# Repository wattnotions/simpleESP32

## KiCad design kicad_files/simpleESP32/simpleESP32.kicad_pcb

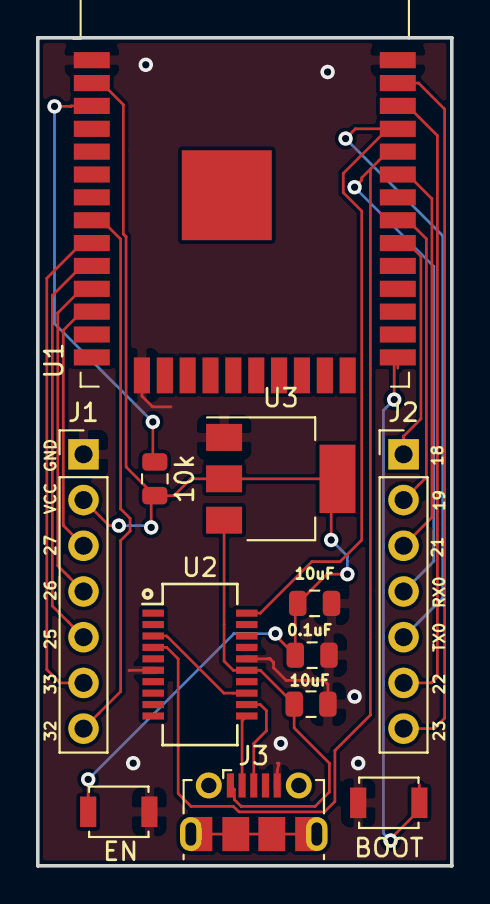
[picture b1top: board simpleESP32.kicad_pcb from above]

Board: 2 copper layers, 23.0 x 46.0 mm, 12 parts (0 on the bottom side), 19 nets.

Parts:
0.1uF: 0.1uF; C_0805_2012Metric
10k: 10K; R_0805_2012Metric
10uF, 10uF#2: 10uF; C_0805_2012Metric
BOOT: BOOT; SW_SPST_B3U-1000P
EN: EN; SW_SPST_B3U-1000P
J1, J2: Conn_01x07; PinHeader_1x07_P2.54mm_Vertical
J3: USB_B_Micro; USB_Micro-B_Molex-105017-0001
U1: ESP32-WROOM-32D; ESP32-WROOM-32
U2: FT231XS; SSOP-20_3.9x8.7mm_P0.635mm
U3: LM1117-3.3; SOT-223-3_TabPin2

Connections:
+3V3: 0.1uF.1, 10k.2, 10uF#2.1, EN.2, J1.2, U1.2, U3.2
+5V: 10uF.1, J3.1, U2.15, U3.3
/DM: J3.3, U2.12
/DP: J3.2, U2.11
/ESP_RXD0: J2.4, U1.34, U2.4
/ESP_TXD0: J2.5, U1.35, U2.20
/IO18: J2.1, U1.30
/IO19: J2.2, U1.31
/IO21: J2.3, U1.33
/IO22: J2.6, U1.36
/IO23: J2.7, U1.37
/IO25: J1.5, U1.10
/IO26: J1.4, U1.11
/IO27: J1.3, U1.12
/IO32: J1.7, U1.8
/IO33: J1.6, U1.9
GND: 0.1uF.2, 10uF.2, 10uF#2.2, BOOT.2, EN.1, J1.1, J3.5, U1.1, U1.15, U1.38, U2.6, U2.16, U3.1
unnamed: 10k.1, U1.3
unnamed: BOOT.1, U1.25

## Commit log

2020-03-11 added core components
2020-03-12 added footprints
2020-03-12 added more footprints, started test layout
2020-03-13 progress with schematic
2020-03-13 schematic completed
2020-03-15 placed components
2020-03-15 began routing
2020-03-18 more routing progress
2020-03-18 finished routing
2020-03-18 changed silkscreen to component vals
2020-03-18 fixed minor silk screen error
